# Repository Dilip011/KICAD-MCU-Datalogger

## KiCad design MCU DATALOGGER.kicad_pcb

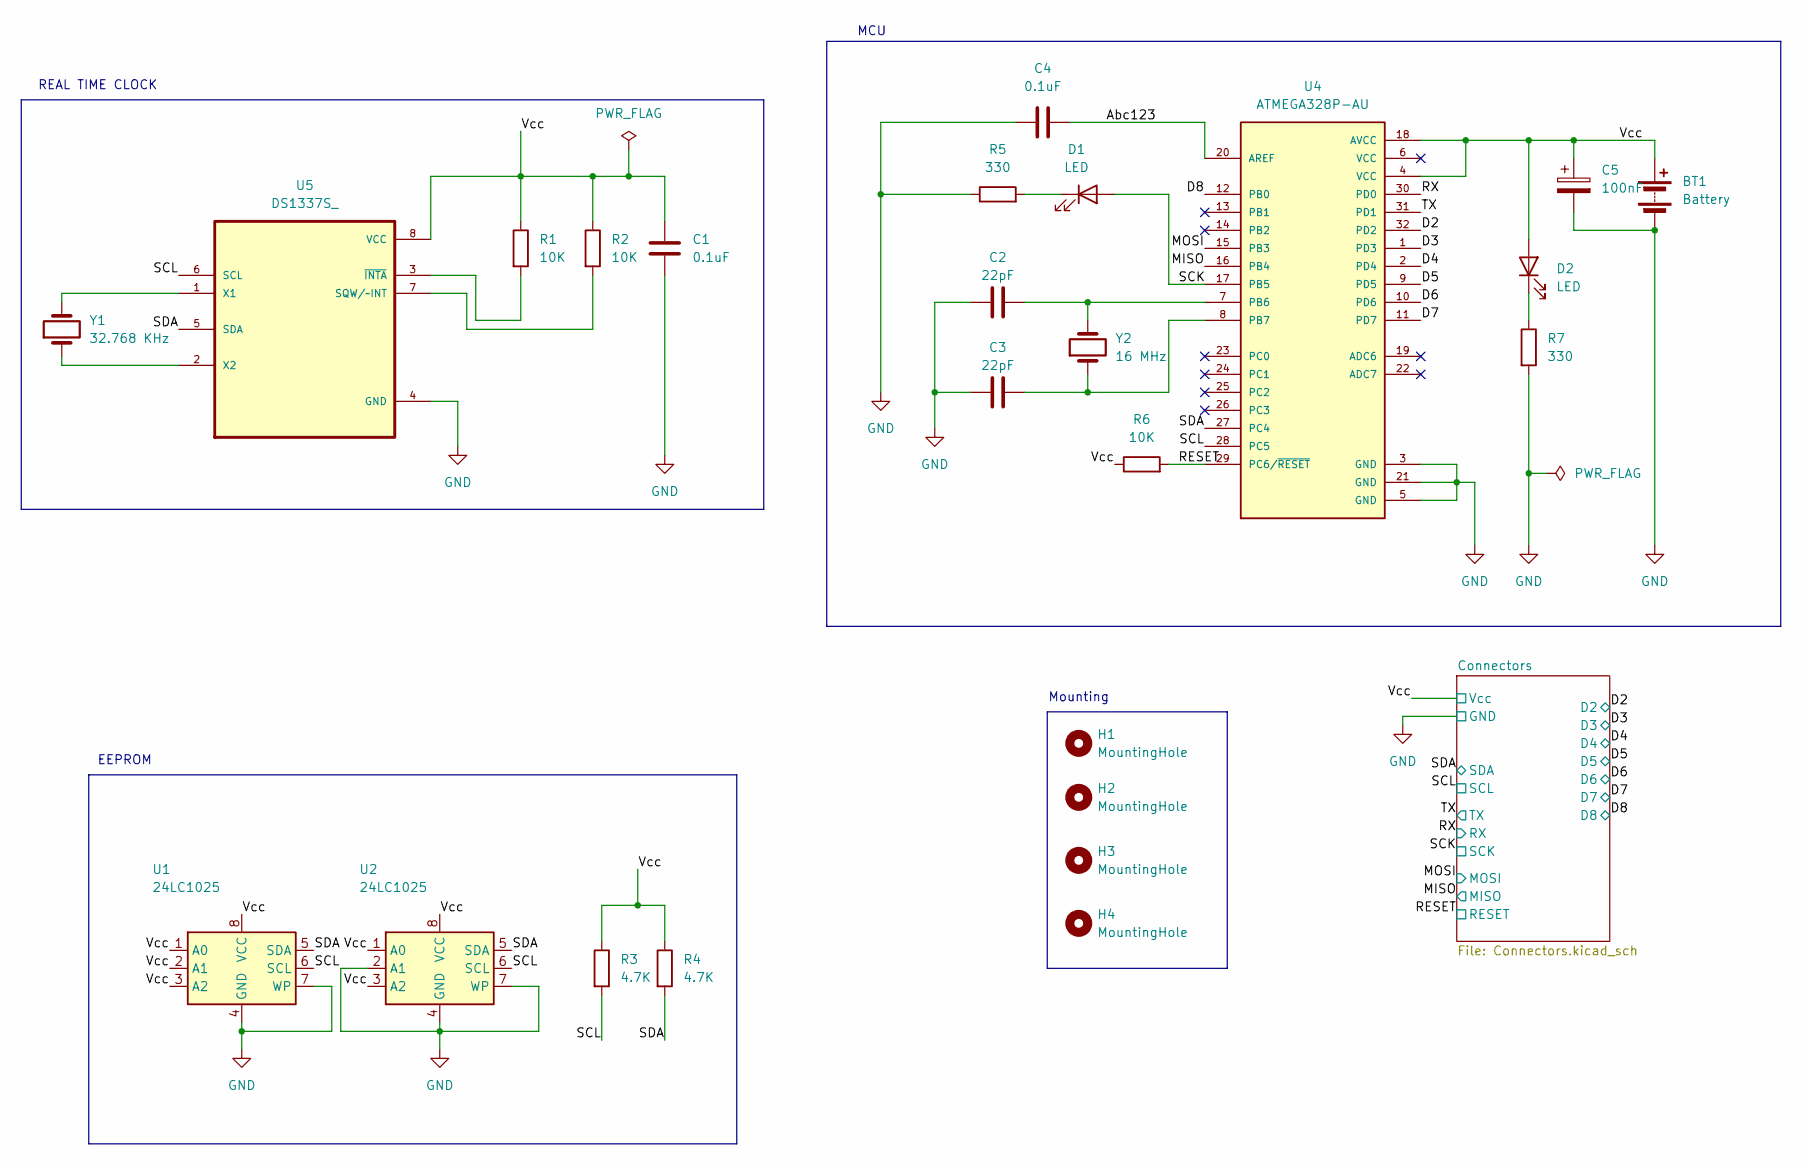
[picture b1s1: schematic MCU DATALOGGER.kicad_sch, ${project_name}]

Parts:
BT1: Battery; PinHeader_1x02_P2.54mm_Vertical
C1, C4: 0.1uF; C_0805_2012Metric
C2, C3: 22pF; C_0805_2012Metric
C5: 100nF; C_0805_2012Metric
D1, D2: LED; LED_0805_2012Metric
H1, H2, H3, H4: MountingHole; MountingHole_2.1mm
R1, R2, R6: 10K; R_0805_2012Metric
R3, R4: 4.7K; R_0805_2012Metric
R5, R7: 330; R_0805_2012Metric
U1, U2: 24LC1025; SOIC-8_5.3x5.3mm_P1.27mm
U4: ATMEGA328P-AU; QFP80P900X900X120-32N; PARTREV 8271A
U5: DS1337S_; SOIC127P600X175-8N
Y1: 32.768 KHz; Crystal_SMD_5032-2Pin_5.0x3.2mm_HandSoldering
Y2: 16 MHz; Crystal_SMD_5032-2Pin_5.0x3.2mm_HandSoldering

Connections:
/Abc123: C4.2, U4.20 (AREF)
/D2: U4.32 (PD2); also elsewhere on the board
/D3: U4.1 (PD3); also elsewhere on the board
/D4: U4.2 (PD4); also elsewhere on the board
/D5: U4.9 (PD5); also elsewhere on the board
/D6: U4.10 (PD6); also elsewhere on the board
/D7: U4.11 (PD7); also elsewhere on the board
/D8: U4.12 (PB0); also elsewhere on the board
/MISO: U4.16 (PB4); also elsewhere on the board
/MOSI: U4.15 (PB3); also elsewhere on the board
/RESET: R6.2, U4.29 (PC6/~RESET); also elsewhere on the board
/RX: U4.30 (PD0); also elsewhere on the board
/SCK: D1.2 (A), U4.17 (PB5); also elsewhere on the board
/SCL: R3.2, U1.6 (SCL), U2.6 (SCL), U4.28 (PC5), U5.6 (SCL); also elsewhere on the board
/SDA: R4.2, U1.5 (SDA), U2.5 (SDA), U4.27 (PC4), U5.5 (SDA); also elsewhere on the board
/TX: U4.31 (PD1); also elsewhere on the board
/Vcc: BT1.1 (+), C1.1, C5.1, D2.2 (A), R1.1, R2.1, R3.1, R4.1, R6.1, U1.1 (A0), U1.2 (A1), U1.3 (A2), U1.8 (VCC), U2.1 (A0), U2.3 (A2), U2.8 (VCC), U4.4 (VCC), U4.18 (AVCC), U5.8 (VCC); also elsewhere on the board
GND: BT1.2 (-), C1.2, C2.1, C3.1, C4.1, C5.2, R5.1, R7.2, U1.4 (GND), U1.7 (WP), U2.2 (A1), U2.4 (GND), U2.7 (WP), U4.3 (GND), U4.5 (GND), U4.21 (GND), U5.4 (GND); also elsewhere on the board
unnamed: D1.1 (K), R5.2
unnamed: D2.1 (K), R7.1
unnamed: C2.2, U4.7 (PB6), Y2.2
unnamed: C3.2, U4.8 (PB7), Y2.1
unnamed: R2.2, U5.7 (SQW/~INT)
unnamed: U5.1 (X1), Y1.2
unnamed: U5.2 (X2), Y1.1
unnamed: R1.2, U5.3 (~INTA)

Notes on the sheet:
REAL TIME CLOCK
EEPROM
Mounting
MCU

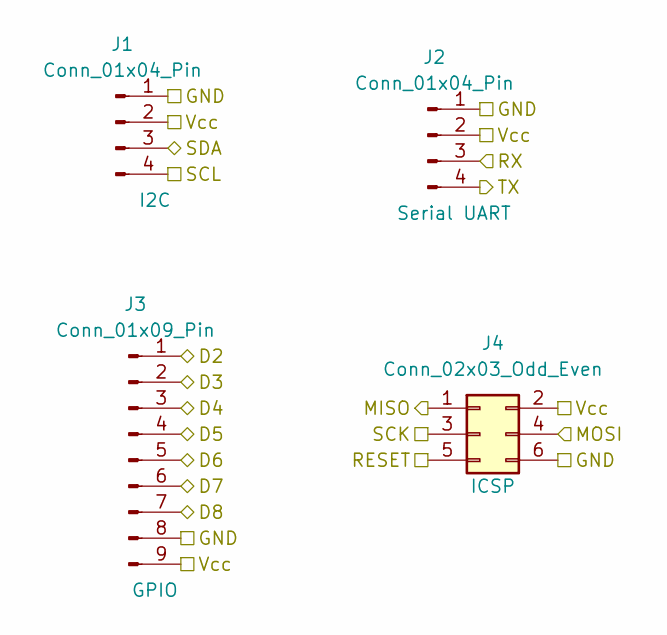
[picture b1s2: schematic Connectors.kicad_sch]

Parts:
J1, J2: Conn_01x04_Pin; PinHeader_1x04_P2.54mm_Vertical
J3: Conn_01x09_Pin; PinHeader_1x09_P2.54mm_Vertical
J4: Conn_02x03_Odd_Even; PinHeader_2x03_P2.54mm_Vertical

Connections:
/D2: J3.1; also elsewhere on the board
/D3: J3.2; also elsewhere on the board
/D4: J3.3; also elsewhere on the board
/D5: J3.4; also elsewhere on the board
/D6: J3.5; also elsewhere on the board
/D7: J3.6; also elsewhere on the board
/D8: J3.7; also elsewhere on the board
/MISO: J4.1; also elsewhere on the board
/MOSI: J4.4; also elsewhere on the board
/RESET: J4.5; also elsewhere on the board
/RX: J2.3; also elsewhere on the board
/SCK: J4.3; also elsewhere on the board
/SCL: J1.4; also elsewhere on the board
/SDA: J1.3; also elsewhere on the board
/TX: J2.4; also elsewhere on the board
/Vcc: J1.2, J2.2, J3.9, J4.2; also elsewhere on the board
GND: J1.1, J2.1, J3.8, J4.6; also elsewhere on the board

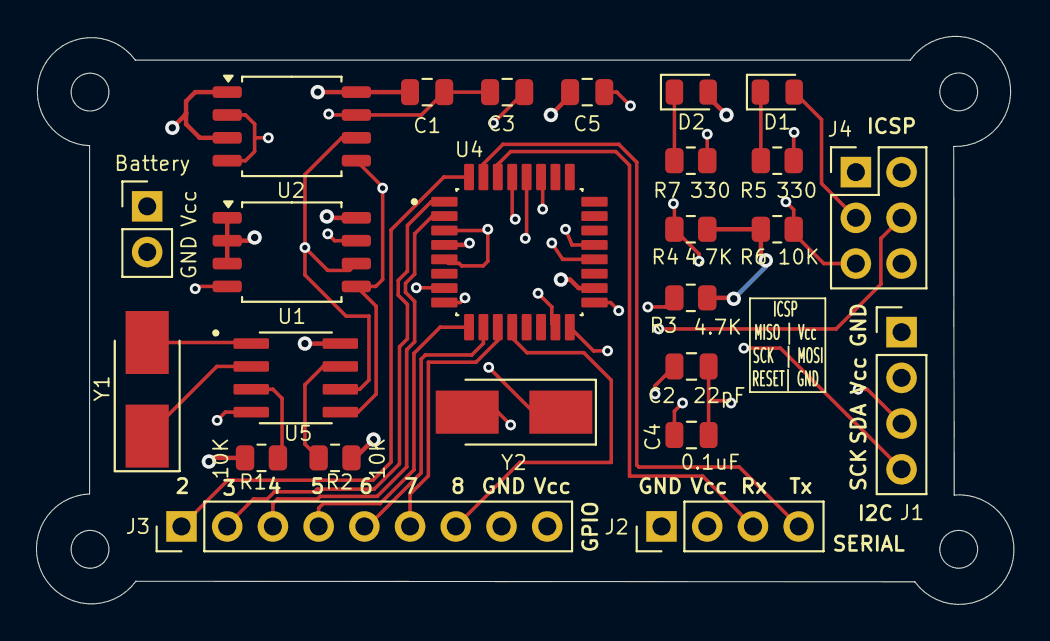
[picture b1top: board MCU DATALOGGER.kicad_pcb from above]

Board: 4 copper layers, 54.3 x 31.6 mm, 29 parts (0 on the bottom side), 26 nets.

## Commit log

2025-05-21 Initial commit of MCU DATALOGGER
2025-05-21 UPDATED WITH GITIGNORE
2025-05-21 updated in 2 layer
2025-05-21 Updated PCB For 2 Layer
2025-05-21 Updated for 2layer
2025-05-22 Updated on 22 may
